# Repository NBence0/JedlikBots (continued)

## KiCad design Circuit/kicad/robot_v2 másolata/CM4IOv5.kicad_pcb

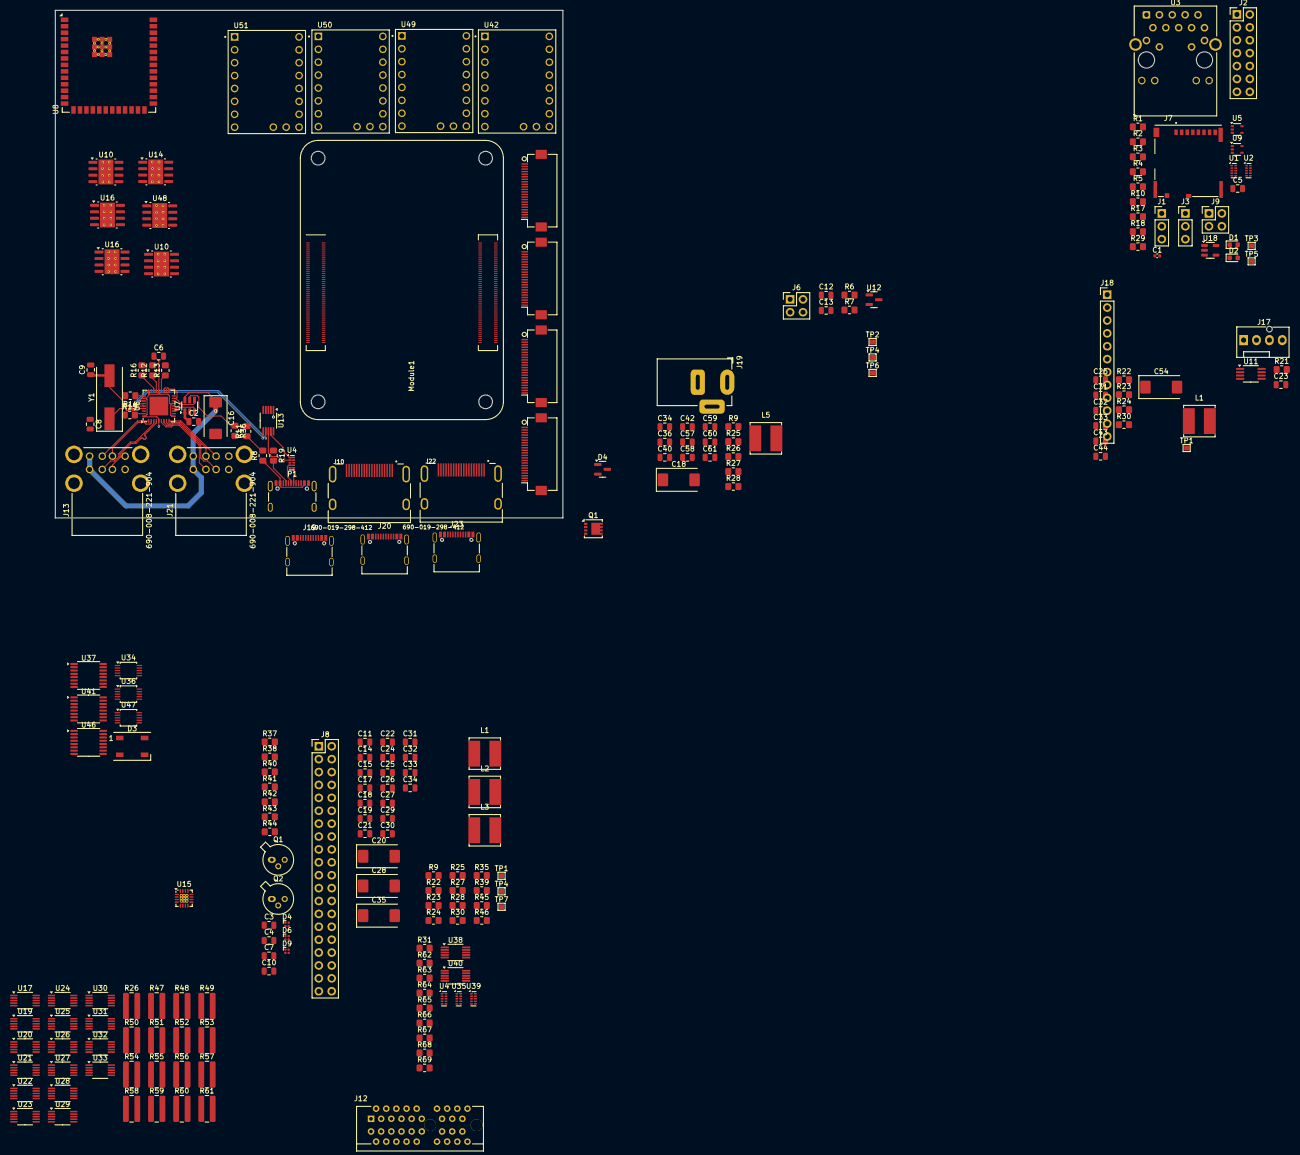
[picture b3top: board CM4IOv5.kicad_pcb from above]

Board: 4 copper layers, 100.0 x 100.0 mm, 226 parts (0 on the bottom side), 295 nets.

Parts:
C1: 100n; C_0402_1005Metric
C2, C5: 10u; C_0805_2012Metric
C3, C7: 100nf; C_0805_2012Metric
C4: 1uf; C_0805_2012Metric
C6: 100u; C_0805_2012Metric
C8, C9: 27pF; C_0805_2012Metric
C10: 100uf; C_0805_2012Metric
C11, C21, C25, C29, C34#2, C42: 10u 35v; C_0805_2012Metric
C12, C13, C14, C15, C22, C23, C24, C30, C31, C31#2, C32, C40, C57, C58: 100n; C_0805_2012Metric
C16, C18#2, C20, C28, C35, C54: 100uF; CP_EIA-7343-31_Kemet-D
C17, C19, C25#2, C27, C32#2, C33#2, C34, C44, C59, C61: nf; C_0805_2012Metric
C18, C26, C33, C43, C60: 1.2nF; C_0805_2012Metric
C36: 100n 100v; C_0805_2012Metric
D1: LED Red; LED_0603_1608Metric
D2: LED Green; LED_0603_1608Metric
D3: WS2812B; LED_WS2812B_PLCC4_5.0x5.0mm_P3.2mm
D4, D6, D9: LED; LED_Lumex_SML-LX0303SIUPGUSB
D4#2: MMBZ5242BLT3G; SOT-23
J1, J3: Conn_01x03; PinHeader_1x03_P2.54mm_Vertical
J2: Conn_02x07_Odd_Even; PinHeader_2x07_P2.54mm_Vertical
J4, J5, J15, J16: Conn_01x22_Female; Hirose_FH12-22S-0.5SH_1x22-1MP_P0.50mm_Horizontal
J6, J9: THD-02-R; PinHeader_2x02_P2.54mm_Vertical
J7: Micro_SD_Card_Det; SDCARD_MOLEX_503398-1892
J8: THD-20-R; PinHeader_2x20_P2.54mm_Vertical
J10, J22: 690-019-298-412; EDAC 690-019-298-412
J12: 10018783-11200TLF; PCIex1-36
J13, J21: 690-008-221-904; MOLEX_USB_67298-4090
J17: Molex 470531000; FanPinHeader_1x04_P2.54mm_Vertical
J18: Conn_01x12_Pin; PinHeader_1x12_P2.54mm_Vertical
J19, J20, J23: USB_C_Receptacle_USB2.0_16P; USB_C_Receptacle_Palconn_UTC16-G
J19#2: Barrel_Jack; BarrelJack_Horizontal
L1, L1#2, L2, L3, L5: SRN6045TA-3R3Y; L_Bourns_SRN6045TA
Module1: ComputeModule4; Raspberry-Pi-4-Compute-Module
P1: USB_C_Plug_USB2.0; USB_C_Receptacle_GCT_USB4105-xx-A_16P_TopMnt_Horizontal
Q1: DMP3013SFV-7; Diodes_PowerDI3333-8
Q1#2, Q2: SS8050-G; TO-18-3_Lens
R1, R10, R37, R38, R44: 1k; R_0805_2012Metric_Pad1.20x1.40mm_HandSolder
R2, R3: 470R; R_0805_2012Metric_Pad1.20x1.40mm_HandSolder
R4, R17, R18: nf; R_0805_2012Metric_Pad1.20x1.40mm_HandSolder
R5: 0R; R_0805_2012Metric_Pad1.20x1.40mm_HandSolder
R6, R7, R8, R11, R28, R28#2, R62, R63, R66, R67: 2.2K 1%; R_0805_2012Metric_Pad1.20x1.40mm_HandSolder
R9, R9#2, R22, R22#2, R35: 10R; R_0805_2012Metric_Pad1.20x1.40mm_HandSolder
R12, R13, R14, R16, R21: 36K 1%; R_0805_2012Metric_Pad1.20x1.40mm_HandSolder
R15, R23, R23#2, R25, R26, R27, R27#2, R29: 12K 1%; R_0805_2012Metric_Pad1.20x1.40mm_HandSolder
R19, R31, R64, R65, R68, R69: 5.1K 1%; R_0805_2012Metric_Pad1.20x1.40mm_HandSolder
R24, R24#2: 47K 1%; R_0805_2012Metric_Pad1.20x1.40mm_HandSolder
R25#2: 20K 1%; R_0805_2012Metric_Pad1.20x1.40mm_HandSolder
R26#2, R47, R48, R49, R50, R51, R52, R53, R54, R55, R56, R57, R58, R59, R60, R61: 0.025Ω; R_1020_2550Metric
R30, R30#2, R36: 15K 1%; R_0805_2012Metric_Pad1.20x1.40mm_HandSolder
R39: 33K 1%; R_0805_2012Metric_Pad1.20x1.40mm_HandSolder
R40, R41, R42, R43: 10k; R_0805_2012Metric_Pad1.20x1.40mm_HandSolder
R45: 13K 1%; R_0805_2012Metric_Pad1.20x1.40mm_HandSolder
R46: 110K 1%; R_0805_2012Metric_Pad1.20x1.40mm_HandSolder
TP1, TP1#2, TP2, TP3, TP4, TP4#2, TP5, TP6, TP7: TestPoint; TestPoint_Pad_1.0x1.0mm
U1, U2, U4, U4#2, U35, U39: TPD4EUSB30; USON-10_2.5x1.0mm_P0.5mm
U3: MagJack-A70-112-331N126; TRJG0926HENL
U5, U9: 74LVC1G07SE-7; SOT-353_SC-70-5
U6: USB2514B-I/M2; QFN-36-1EP_6x6mm_P0.5mm_EP3.7x3.7mm
U7: AP22653W6; SOT-23-6
U8: ESP32-S3-WROOM-2
U10, U10#2, U14, U16, U16#2, U48: AP64501SP-13; SOIC-8-1EP_3.9x4.9mm_P1.27mm_EP2.95x4.9mm_Mask2.71x3.4mm_Th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
U11: EMC2301-1-ACZL-TR; MSOP-8_3x3mm_P0.65mm
U12: RT9742SNGV; SOT-23
U13, U38, U40: FSUSB42MUX; MSOP-10_3x3mm_P0.5mm
U15: CH343P; QFN-16-1EP_3x3mm_P0.5mm_EP1.7x1.7mm_ThermalVias
U17, U19, U20, U21, U22, U23, U24, U25, U26, U27, U28, U29, U30, U31, U32, U33: INA226; VSSOP-10_3x3mm_P0.5mm
U18: RT9742GGJ5; SOT-23-5
U34, U36, U47: ADS1115IDGS; TSSOP-10_3x3mm_P0.5mm
U37, U41, U46: ADC1283; TSSOP-16_4.4x5mm_P0.65mm
U42, U49, U50, U51: TMC2240_SILENTSTEPSTICK; MODULE_TMC2209_SILENTSTEPSTICK
Y1: 24MHz; Crystal_SMD_HC49-SD

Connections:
5V1: U17.1 (A1), U17.2 (A0), U17.6 (VS), U19.1 (A1), U19.6 (VS), U20.6 (VS), U21.6 (VS), U22.2 (A0), U22.6 (VS), U23.6 (VS), U24.1 (A1), U24.6 (VS), U25.6 (VS), U26.2 (A0), U26.6 (VS), U27.6 (VS), U28.6 (VS), U29.6 (VS), U30.6 (VS), U31.6 (VS), U32.1 (A1), U32.6 (VS), U33.2 (A0), U33.6 (VS)
/+3.3v: D1.2 (A), D2.2 (A), J4.22, J5.22, J8.1, J8.17, J15.22, J16.22, J18.4, Module1.84 (+3.3v_(Output)), Module1.86 (+3.3v_(Output)), R5.1, R17.1, R29.1, U3.15 (LEDG_A), U3.17 (LEDY_A), U5.5 (VCC), U18.5 (IN)
/+5v: C12.1, C18#2.1, C61.1, J8.2, J8.4, J18.3, L5.2, Module1.77 (+5v_(Input)), Module1.79 (+5v_(Input)), Module1.81 (+5v_(Input)), Module1.83 (+5v_(Input)), Module1.85 (+5v_(Input)), Module1.87 (+5v_(Input)), R27.1, TP4.1, U9.5 (VCC), U12.1 (IN)
/+12v: C34#2.1, C40.1, C42.1, D4#2.3 (K), J18.2, Q1.1 (S), Q1.2 (S), Q1.3 (S), TP2.1, U16.2 (VIN), U16.3 (EN)
/CM4_GPIO ( Ethernet, GPIO, SDCARD)/+1.8v: Module1.88 (+1.8v_(Output)), Module1.90 (+1.8v_(Output)), R4.1
/CM4_GPIO ( Ethernet, GPIO, SDCARD)/AIN0: J2.5, Module1.96 (AnalogIP0)
/CM4_GPIO ( Ethernet, GPIO, SDCARD)/AIN1: J2.6, Module1.94 (AnalogIP1)
/CM4_GPIO ( Ethernet, GPIO, SDCARD)/BT_nDis: J3.3, Module1.91 (BT_nDisable)
/CM4_GPIO ( Ethernet, GPIO, SDCARD)/EEPROM_nWP: J2.4, Module1.20 (EEPROM_nWP)
/CM4_GPIO ( Ethernet, GPIO, SDCARD)/ETH_LEDG: Module1.17 (Ethernet_nLED2(3.3v)), R2.2
/CM4_GPIO ( Ethernet, GPIO, SDCARD)/ETH_LEDY: Module1.15 (Ethernet_nLED3(3.3v)), R3.2
/CM4_GPIO ( Ethernet, GPIO, SDCARD)/GLOBAL_EN: J1.1, J2.14, Module1.99 (Global_EN)
/CM4_GPIO ( Ethernet, GPIO, SDCARD)/GPIO2: J8.3, Module1.58 (GPIO2)
/CM4_GPIO ( Ethernet, GPIO, SDCARD)/GPIO3: J8.5, Module1.56 (GPIO3)
/CM4_GPIO ( Ethernet, GPIO, SDCARD)/GPIO4: J8.7, Module1.54 (GPIO4)
/CM4_GPIO ( Ethernet, GPIO, SDCARD)/GPIO5: J8.29, Module1.34 (GPIO5)
/CM4_GPIO ( Ethernet, GPIO, SDCARD)/GPIO6: J8.31, Module1.30 (GPIO6)
/CM4_GPIO ( Ethernet, GPIO, SDCARD)/GPIO7: J8.26, Module1.37 (GPIO7)
/CM4_GPIO ( Ethernet, GPIO, SDCARD)/GPIO8: J8.24, Module1.39 (GPIO8)
/CM4_GPIO ( Ethernet, GPIO, SDCARD)/GPIO9: J8.21, Module1.40 (GPIO9)
/CM4_GPIO ( Ethernet, GPIO, SDCARD)/GPIO10: J8.19, Module1.44 (GPIO10)
/CM4_GPIO ( Ethernet, GPIO, SDCARD)/GPIO11: J8.23, Module1.38 (GPIO11)
/CM4_GPIO ( Ethernet, GPIO, SDCARD)/GPIO12: J8.32, Module1.31 (GPIO12)
/CM4_GPIO ( Ethernet, GPIO, SDCARD)/GPIO13: J8.33, Module1.28 (GPIO13)
/CM4_GPIO ( Ethernet, GPIO, SDCARD)/GPIO14: J8.8, Module1.55 (GPIO14)
/CM4_GPIO ( Ethernet, GPIO, SDCARD)/GPIO15: J8.10, Module1.51 (GPIO15)
/CM4_GPIO ( Ethernet, GPIO, SDCARD)/GPIO16: J8.36, Module1.29 (GPIO16)
/CM4_GPIO ( Ethernet, GPIO, SDCARD)/GPIO17: J8.11, Module1.50 (GPIO17)
/CM4_GPIO ( Ethernet, GPIO, SDCARD)/GPIO18: J8.12, Module1.49 (GPIO18)
/CM4_GPIO ( Ethernet, GPIO, SDCARD)/GPIO19: J8.35, Module1.26 (GPIO19)
/CM4_GPIO ( Ethernet, GPIO, SDCARD)/GPIO20: J8.38, Module1.27 (GPIO20)
/CM4_GPIO ( Ethernet, GPIO, SDCARD)/GPIO21: J8.40, Module1.25 (GPIO21)
/CM4_GPIO ( Ethernet, GPIO, SDCARD)/GPIO22: J8.15, Module1.46 (GPIO22)
/CM4_GPIO ( Ethernet, GPIO, SDCARD)/GPIO23: J8.16, Module1.47 (GPIO23)
/CM4_GPIO ( Ethernet, GPIO, SDCARD)/GPIO24: J8.18, Module1.45 (GPIO24)
/CM4_GPIO ( Ethernet, GPIO, SDCARD)/GPIO25: J8.22, Module1.41 (GPIO25)
/CM4_GPIO ( Ethernet, GPIO, SDCARD)/GPIO26: J8.37, Module1.24 (GPIO26)
/CM4_GPIO ( Ethernet, GPIO, SDCARD)/GPIO27: J8.13, Module1.48 (GPIO27)
/CM4_GPIO ( Ethernet, GPIO, SDCARD)/GPIO_VREF: Module1.78 (GPIO_VREF(1.8v/3.3v_Input)), R4.2, R5.2, R6.1, R7.1
/CM4_GPIO ( Ethernet, GPIO, SDCARD)/ID_SC: J6.1, J8.28, Module1.35 (ID_SC)
/CM4_GPIO ( Ethernet, GPIO, SDCARD)/ID_SD: J6.3, J8.27, Module1.36 (ID_SD)
/CM4_GPIO ( Ethernet, GPIO, SDCARD)/RUN_PG: J1.3, Module1.92 (RUN_PG), U9.2
/CM4_GPIO ( Ethernet, GPIO, SDCARD)/Reserved: Module1.76 (Reserved), R18.1
/CM4_GPIO ( Ethernet, GPIO, SDCARD)/SD_CLK: J7.5 (CLK), Module1.57 (SD_CLK)
/CM4_GPIO ( Ethernet, GPIO, SDCARD)/SD_CMD: J7.3 (CMD), Module1.62 (SD_CMD)
/CM4_GPIO ( Ethernet, GPIO, SDCARD)/SD_DAT0: J7.7 (DAT0), Module1.63 (SD_DAT0)
/CM4_GPIO ( Ethernet, GPIO, SDCARD)/SD_DAT1: J7.8 (DAT1), Module1.67 (SD_DAT1)
/CM4_GPIO ( Ethernet, GPIO, SDCARD)/SD_DAT2: J7.1 (DAT2), Module1.69 (SD_DAT2)
/CM4_GPIO ( Ethernet, GPIO, SDCARD)/SD_DAT3: J7.2 (DAT3/CD), Module1.61 (SD_DAT3)
/CM4_GPIO ( Ethernet, GPIO, SDCARD)/SD_PWR: C5.1, J7.4 (VDD), U18.1 (OUT)
/CM4_GPIO ( Ethernet, GPIO, SDCARD)/SD_PWR_ON: Module1.75 (SD_PWR_ON), R29.2, U18.4 (EN)
/CM4_GPIO ( Ethernet, GPIO, SDCARD)/SYNC_IN: J2.8, Module1.16 (Ethernet_SYNC_IN(1.8v))
/CM4_GPIO ( Ethernet, GPIO, SDCARD)/SYNC_OUT: J2.9, Module1.18 (Ethernet_SYNC_OUT(1.8v))
/CM4_GPIO ( Ethernet, GPIO, SDCARD)/TR0_TAP: J9.3, U3.11 (VC1)
/CM4_GPIO ( Ethernet, GPIO, SDCARD)/TR1_TAP: J9.1, U3.12 (VC2)
/CM4_GPIO ( Ethernet, GPIO, SDCARD)/TR2_TAP: J9.2, U3.13 (VC3)
/CM4_GPIO ( Ethernet, GPIO, SDCARD)/TR3_TAP: J9.4, U3.14 (VC4)
/CM4_GPIO ( Ethernet, GPIO, SDCARD)/TRD0_N: Module1.10 (Ethernet_Pair0_N), U2.4 (D2+), U2.7, U3.2 (TRD0-)
/CM4_GPIO ( Ethernet, GPIO, SDCARD)/TRD0_P: Module1.12 (Ethernet_Pair0_P), U2.5 (D2-), U2.6, U3.1 (TRD0+)
/CM4_GPIO ( Ethernet, GPIO, SDCARD)/TRD1_N: Module1.6 (Ethernet_Pair1_N), U2.2 (D1-), U2.9, U3.6 (TRD1-)
/CM4_GPIO ( Ethernet, GPIO, SDCARD)/TRD1_P: Module1.4 (Ethernet_Pair1_P), U2.1 (D1+), U2.10, U3.3 (TRD1+)
/CM4_GPIO ( Ethernet, GPIO, SDCARD)/TRD2_N: Module1.9 (Ethernet_Pair2_N), U1.4 (D2+), U1.7, U3.8 (TRD2-)
/CM4_GPIO ( Ethernet, GPIO, SDCARD)/TRD2_P: Module1.11 (Ethernet_Pair2_P), U1.5 (D2-), U1.6, U3.7 (TRD2+)
/CM4_GPIO ( Ethernet, GPIO, SDCARD)/TRD3_N: Module1.5 (Ethernet_Pair3_N), U1.2 (D1-), U1.9, U3.10 (TRD3-)
/CM4_GPIO ( Ethernet, GPIO, SDCARD)/TRD3_P: Module1.3 (Ethernet_Pair3_P), U1.1 (D1+), U1.10, U3.9 (TRD3+)
/CM4_GPIO ( Ethernet, GPIO, SDCARD)/TV_OUT: J2.11, Module1.111 (VDAC_COMP)
/CM4_GPIO ( Ethernet, GPIO, SDCARD)/WL_nDis: J3.1, Module1.89 (WiFi_nDisable)
/CM4_GPIO ( Ethernet, GPIO, SDCARD)/nPWR_LED: Module1.95 (nPI_LED_PWR), U5.2
/CM4_GPIO ( Ethernet, GPIO, SDCARD)/nRPIBOOT: J2.2, Module1.93 (nRPIBOOT)
/CM4_HighSpeed/CAM0_C_N: J4.8, Module1.140 (CAM0_C_N)
/CM4_HighSpeed/CAM0_C_P: J4.9, Module1.142 (CAM0_C_P)
/CM4_HighSpeed/CAM0_D0_N: J4.2, Module1.128 (CAM0_D0_N)
/CM4_HighSpeed/CAM0_D0_P: J4.3, Module1.130 (CAM0_D0_P)
/CM4_HighSpeed/CAM0_D1_N: J4.5, Module1.134 (CAM0_D1_N)
/CM4_HighSpeed/CAM0_D1_P: J4.6, Module1.136 (CAM0_D1_P)
/CM4_HighSpeed/CAM1_C_N: J5.8, Module1.127 (CAM1_C_N)
/CM4_HighSpeed/CAM1_C_P: J5.9, Module1.129 (CAM1_C_P)
/CM4_HighSpeed/CAM1_D0_N: J5.2, Module1.115 (CAM1_D0_N)
/CM4_HighSpeed/CAM1_D0_P: J5.3, Module1.117 (CAM1_D0_P)
/CM4_HighSpeed/CAM1_D1_N: J5.5, Module1.121 (CAM1_D1_N)
/CM4_HighSpeed/CAM1_D1_P: J5.6, Module1.123 (CAM1_D1_P)
/CM4_HighSpeed/CAM1_D2_N: J5.11, Module1.133 (CAM1_D2_N)
/CM4_HighSpeed/CAM1_D2_P: J5.12, Module1.135 (CAM1_D2_P)
/CM4_HighSpeed/CAM1_D3_N: J5.14, Module1.139 (CAM1_D3_N)
/CM4_HighSpeed/CAM1_D3_P: J5.15, Module1.141 (CAM1_D3_P)
/CM4_HighSpeed/CAM_GPIO: J4.17, J5.17, Module1.97 (Camera_GPIO)
/CM4_HighSpeed/DSI0_C_N: J15.8, Module1.169 (DSI0_C_N)
/CM4_HighSpeed/DSI0_C_P: J15.9, Module1.171 (DSI0_C_P)
/CM4_HighSpeed/DSI0_D0_N: J15.2, Module1.157 (DSI0_D0_N)
/CM4_HighSpeed/DSI0_D0_P: J15.3, Module1.159 (DSI0_D0_P)
/CM4_HighSpeed/DSI0_D1_N: J15.5, Module1.163 (DSI0_D1_N)
/CM4_HighSpeed/DSI0_D1_P: J15.6, Module1.165 (DSI0_D1_P)
/CM4_HighSpeed/DSI1_C_N: J16.8, Module1.187 (DSI1_C_N)
/CM4_HighSpeed/DSI1_C_P: J16.9, Module1.189 (DSI1_C_P)
/CM4_HighSpeed/DSI1_D0_N: J16.2, Module1.175 (DSI1_D0_N)
/CM4_HighSpeed/DSI1_D0_P: J16.3, Module1.177 (DSI1_D0_P)
/CM4_HighSpeed/DSI1_D1_N: J16.5, Module1.181 (DSI1_D1_N)
/CM4_HighSpeed/DSI1_D1_P: J16.6, Module1.183 (DSI1_D1_P)
/CM4_HighSpeed/DSI1_D2_N: J16.11, Module1.193 (DSI1_D2_N)
/CM4_HighSpeed/DSI1_D2_P: J16.12, Module1.195 (DSI1_D2_P)
/CM4_HighSpeed/DSI1_D3_N: J16.14, Module1.194 (DSI1_D3_N)
/CM4_HighSpeed/DSI1_D3_P: J16.15, Module1.196 (DSI1_D3_P)
/CM4_HighSpeed/HDMI0_CEC: J22.13 (CEC), Module1.151 (HDMI0_CEC)
/CM4_HighSpeed/HDMI0_CK_N: J22.12 (CK-), Module1.190 (HDMI0_CLK_N)
/CM4_HighSpeed/HDMI0_CK_P: J22.10 (CK+), Module1.188 (HDMI0_CLK_P)
/CM4_HighSpeed/HDMI0_D0_N: J22.9 (D0-), Module1.184 (HDMI0_TX0_N)
/CM4_HighSpeed/HDMI0_D0_P: J22.7 (D0+), Module1.182 (HDMI0_TX0_P)
/CM4_HighSpeed/HDMI0_D1_N: J22.6 (D1-), Module1.178 (HDMI0_TX1_N)
/CM4_HighSpeed/HDMI0_D1_P: J22.4 (D1+), Module1.176 (HDMI0_TX1_P)
/CM4_HighSpeed/HDMI0_D2_N: J22.3 (D2-), Module1.172 (HDMI0_TX2_N)
/CM4_HighSpeed/HDMI0_D2_P: J22.1 (D2+), Module1.170 (HDMI0_TX2_P)
/CM4_HighSpeed/HDMI0_HOTPLUG: J22.19 (HPD/HEAC-), Module1.153 (HDMI0_HOTPLUG)
/CM4_HighSpeed/HDMI0_SCL: J22.15 (SCL), Module1.200 (HDMI0_SCL)
/CM4_HighSpeed/HDMI0_SDA: J22.16 (SDA), Module1.199 (HDMI0_SDA)
/CM4_HighSpeed/HDMI1_CEC: J10.13 (CEC), Module1.149 (HDMI1_CEC)
/CM4_HighSpeed/HDMI1_CK_N: J10.12 (CK-), Module1.166 (HDMI1_CLK_N)
/CM4_HighSpeed/HDMI1_CK_P: J10.10 (CK+), Module1.164 (HDMI1_CLK_P)
/CM4_HighSpeed/HDMI1_D0_N: J10.9 (D0-), Module1.160 (HDMI1_TX0_N)
/CM4_HighSpeed/HDMI1_D0_P: J10.7 (D0+), Module1.158 (HDMI1_TX0_P)
/CM4_HighSpeed/HDMI1_D1_N: J10.6 (D1-), Module1.154 (HDMI1_TX1_N)
/CM4_HighSpeed/HDMI1_D1_P: J10.4 (D1+), Module1.152 (HDMI1_TX1_P)
/CM4_HighSpeed/HDMI1_D2_N: J10.3 (D2-), Module1.148 (HDMI1_TX2_N)
/CM4_HighSpeed/HDMI1_D2_P: J10.1 (D2+), Module1.146 (HDMI1_TX2_P)
/CM4_HighSpeed/HDMI1_HOTPLUG: J10.19 (HPD/HEAC-), Module1.143 (HDMI1_HOTPLUG)
/CM4_HighSpeed/HDMI1_SCL: J10.15 (SCL), Module1.147 (HDMI1_SCL)
/CM4_HighSpeed/HDMI1_SDA: J10.16 (SDA), Module1.145 (HDMI1_SDA)
/CM4_HighSpeed/HDMI_5v: C13.1, J10.18 (+5V), J22.18 (+5V), U12.2 (OUT)
/CM4_HighSpeed/PCIE_CLK_N: J18.10, Module1.112 (PCIe_CLK_N)
/CM4_HighSpeed/PCIE_CLK_P: J18.9, Module1.110 (PCIe_CLK_P)
/CM4_HighSpeed/PCIE_CLK_nREQ: J18.12, Module1.102 (PCIe_CLK_nREQ)
/CM4_HighSpeed/PCIE_RX_N: J18.8, Module1.118 (PCIe_RX_N)
/CM4_HighSpeed/PCIE_RX_P: J18.7, Module1.116 (PCIe_RX_P)
/CM4_HighSpeed/PCIE_TX_N: J18.6, Module1.124 (PCIe_TX_N)
/CM4_HighSpeed/PCIE_TX_P: J18.5, Module1.122 (PCIe_TX_P)
/CM4_HighSpeed/PCIE_nRST: J18.11, Module1.109 (PCIe_nRST)
/CM4_HighSpeed/SCL0: J5.20, J16.20, Module1.80 (SCL0), U11.2 (SCL)
/CM4_HighSpeed/SCL1: J4.20, J6.2, J15.20, R7.2
/CM4_HighSpeed/SDA0: J5.21, J16.21, Module1.82 (SDA0), U11.1 (SDA)
/CM4_HighSpeed/SDA1: J4.21, J6.4, J15.21, R6.2
/CM4_HighSpeed/USB2_N: Module1.103 (USB2_N), U13.4 (D_N)
/CM4_HighSpeed/USB2_P: Module1.105 (USB2_P), U13.3 (D_P)
/CM4_HighSpeed/USBOTG_ID: Module1.101 (USB_OTG_ID), R8.2, R11.1, U13.2 (SEL)
/FAN/+3.3v: C23.1, R21.2, U11.3 (VDD)
/INA226/+1000000: R48.1, U20.8 (Vbus), U20.10 (Vin+)
/INA226/+1000001: R61.1, U33.8 (Vbus), U33.10 (Vin+)
/INA226/+1000010: R58.1, U30.8 (Vbus), U30.10 (Vin+)
/INA226/+1000011: R57.1, U29.8 (Vbus), U29.10 (Vin+)
/INA226/+1000100: R52.1, U24.8 (Vbus), U24.10 (Vin+)
/INA226/+1000101: R26#2.1, U17.8 (Vbus), U17.10 (Vin+)
/INA226/+1000110: R60.1, U32.8 (Vbus), U32.10 (Vin+)
/INA226/+1000111: R47.1, U19.8 (Vbus), U19.10 (Vin+)
/INA226/+1001000: R56.1, U28.8 (Vbus), U28.10 (Vin+)
/INA226/+1001001: R50.1, U22.8 (Vbus), U22.10 (Vin+)
/INA226/+1001010: R49.1, U21.8 (Vbus), U21.10 (Vin+)
/INA226/+1001011: R51.1, U23.8 (Vbus), U23.10 (Vin+)
/INA226/+1001100: R59.1, U31.8 (Vbus), U31.10 (Vin+)
/INA226/+1001101: R54.1, U26.8 (Vbus), U26.10 (Vin+)
/INA226/+1001110: R53.1, U25.8 (Vbus), U25.10 (Vin+)
/INA226/+1001111: R55.1, U27.8 (Vbus), U27.10 (Vin+)
/INA226/-1000000: R48.2, U20.9 (Vin-)
/INA226/-1000001: R61.2, U33.9 (Vin-)
/INA226/-1000010: R58.2, U30.9 (Vin-)
/INA226/-1000011: R57.2, U29.9 (Vin-)
/INA226/-1000100: R52.2, U24.9 (Vin-)
/INA226/-1000101: R26#2.2, U17.9 (Vin-)
/INA226/-1000110: R60.2, U32.9 (Vin-)
/INA226/-1000111: R47.2, U19.9 (Vin-)
/INA226/-1001000: R56.2, U28.9 (Vin-)
/INA226/-1001001: R50.2, U22.9 (Vin-)
/INA226/-1001010: R49.2, U21.9 (Vin-)
/INA226/-1001011: R51.2, U23.9 (Vin-)
/INA226/-1001100: R59.2, U31.9 (Vin-)
/INA226/-1001101: R54.2, U26.9 (Vin-)
/INA226/-1001110: R53.2, U25.9 (Vin-)
/INA226/-1001111: R55.2, U27.9 (Vin-)
/INA226/alert out: U17.3 (~Alert), U19.3 (~Alert), U20.3 (~Alert), U21.3 (~Alert), U22.3 (~Alert), U23.3 (~Alert), U24.3 (~Alert), U25.3 (~Alert), U26.3 (~Alert), U27.3 (~Alert), U28.3 (~Alert), U29.3 (~Alert), U30.3 (~Alert), U31.3 (~Alert), U32.3 (~Alert), U33.3 (~Alert)
/PCIe-connector/+3.3v: C44.1, C54.1, J12.A5 (TCK), J12.A6 (TDI), J12.A8 (TMS), J12.A9 (+3.3V), J12.A10 (+3.3V), J12.B8 (+3.3v), J12.B9 (nTRST), J12.B10 (+3.3vAUX), L1.2, R24.1, TP1#2.1
/PCIe-connector/+12v: C25.1, J12.A2 (+12V), J12.A3 (+12V), J12.B1 (+12v), J12.B2 (+12v), J12.B3 (+12v), U10#2.2 (VIN), U10#2.3 (EN)
/PSUs/3V3: C27.1, C28.1, L1#2.2, R24#2.1, TP1.1
/PSUs/5v: C19.1, C20.1, L2.2, R27#2.1, TP4#2.1
/PSUs/7V5: C34.1, C35.1, L3.2, R45.1, TP7.1
/PSUs/input voltage: C11.1, C21.1, C29.1, U10.2 (VIN), U14.2 (VIN), U16#2.2 (VIN)
/USB2-HUB/+3.3v: C6.1, U6.5 (VDDA33), U6.10 (VDDA33), U6.15 (VDD33), U6.23 (VDD33), U6.27 (VBUS_DET), U6.29 (VDDA33), U6.36 (VDDA33), U13.1 (VCC), U38.1 (VCC), U40.1 (VCC)
/USB2-HUB/+5v: C2.1, U7.1 (IN)
/USB2-HUB/CH343P_usbD+: U15.7 (UD+), U40.3 (D_P)
/USB2-HUB/CH343P_usbD-: U15.8 (UD-), U40.4 (D_N)
/USB2-HUB/ESP_usbD+: U8.14 (USB_D+/IO20), U38.3 (D_P)
/USB2-HUB/ESP_usbD-: U8.13 (USB_D-/IO19), U38.4 (D_N)
/USB2-HUB/HD1_N: J13.2 (D-`), U6.1 (USBDM_DN1/PRT_DIS_M1), U35.5 (D2-), U35.6
/USB2-HUB/HD1_P: J13.3 (D+`), U6.2 (USBDP_DN1/PRT_DIS_P1), U35.4 (D2+), U35.7
/USB2-HUB/HD2_N: J13.6 (D-), U6.3 (USBDM_DN2/PRT_DIS_M2), U35.2 (D1-), U35.9
/USB2-HUB/HD2_P: J13.7 (D+), U6.4 (USBDP_DN2/PRT_DIS_P2), U35.1 (D1+), U35.10
/USB2-HUB/HD3_N: J21.6 (D-), U6.6 (USBDM_DN3/PRT_DIS_M3), U40.6 (HSD0_M)
/USB2-HUB/HD3_P: J21.7 (D+), U6.7 (USBDP_DN3/PRT_DIS_P3), U40.7 (HSD0_P)
/USB2-HUB/HD4_N: J21.2 (D-`), U6.8 (USBDM_DN4/PRT_DIS_M4), U38.6 (HSD0_M)
/USB2-HUB/HD4_P: J21.3 (D+`), U6.9 (USBDP_DN4/PRT_DIS_P4), U38.7 (HSD0_P)
/USB2-HUB/PWR1: U6.12 (PRTPWR1/BC_EN1), U7.3 (EN)
/USB2-HUB/USBD_N: J23.A6 (D+), J23.B6 (D+), U4.2 (D1-), U4.9, U4#2.2 (D1-), U4#2.9, U13.8 (HSD1_M)
/USB2-HUB/USBD_P: J23.A7 (D-), J23.B7 (D-), U4.1 (D1+), U4.10, U4#2.1 (D1+), U4#2.10, U13.9 (HSD1_P)
/USB2-HUB/USBH_N: U6.30 (USBDM_UP), U13.6 (HSD0_M)
/USB2-HUB/USBH_P: U6.31 (USBDP_UP), U13.7 (HSD0_P)
/USB2-HUB/VBUS: C16.1, J13.1 (VBUS`), J13.5 (VBUS), J21.1 (VBUS`), J21.5 (VBUS), U7.6 (OUT)
/USB2-HUB/nOCS1: U6.13 (OCS_N1), U6.17 (OCS_N2), U6.19 (OCS_N3), U6.21 (OCS_N4), U7.4 (nFault)
/YD-ESP32-S3/3v3-input: C7.1, C10.1, R37.2, R38.2, R42.2, R43.1, R44.2, U8.2 (3V3), U15.1 (VIO)
/YD-ESP32-S3/5 v In: U15.3 (VDD5), U15.9 (VBUS)
/YD-ESP32-S3/esp32_chip_pu: C4.1, Q2.3 (C), R42.1, U8.3 (EN)
/YD-ESP32-S3/esp32_gpio0: Q1#2.3 (C), U8.27 (IO0)
/YD-ESP32-S3/esp_rxd0: D9.1 (K), U8.36 (RXD0/IO44)
/YD-ESP32-S3/esp_txd0: D6.1 (K), U8.37 (TXD0/IO43), U15.4 (TXD), U15.5 (RXD)
/nEXTRST: Module1.100 (nEXTRST), U6.26 (RESET_N)
GND: C1.2, C2.2, C3.2, C4.2, C5.2, C6.2, C7.2, C8.2, C9.2, C10.2, C11.2, C12.2, C13.2, C15.2, C16.2, C17.2, C18.2, C18#2.2, C20.2, C21.2, C23.2, C24.2, C25.2, C25#2.2, C26.2, C28.2, C29.2, C31#2.2, C32.2, C32#2.2, C33.2, C33#2.2, C34#2.2, C35.2, C36.2, C42.2, C43.2, C54.2, C58.2, C59.2, C60.2, J1.2, J2.1, J2.3, J2.7, J2.10, J2.12, J3.2, J4.1, J4.4, J4.7, J4.10, J4.13, J4.16, J4.19, J5.1, J5.4, J5.7, J5.10, J5.13, J5.16, J5.19, J7.6 (VSS), J7.11 (SHIELD), J8.6, J8.9, J8.14, J8.20, J8.25, J8.30, J8.34, J8.39, J10.2 (D2S), J10.5 (D1S), J10.8 (D0S), J10.11 (CKS), J10.17 (GND), J10.SH1 (SH), J10.SH2 (SH), J10.SH3 (SH), J10.SH4 (SH), J12.A4 (GND), J12.A12 (GND), J12.A15 (GND), J12.A18 (GND), J12.B4 (GND), J12.B7 (GND), J12.B13 (GND), J12.B16 (GND), J12.B18 (GND), J13.4 (GND`), J13.8 (GND), J13.MT1, J13.MT2, J13.MT3, J13.MT4, J15.1, J15.4, J15.7, J15.10, J15.13, J15.16, J15.19, J16.1, J16.4, J16.7, J16.10, J16.13, J16.16, J16.19, J17.1, J18.1, J19.A1 (GND), J19.A12 (GND), J19.B1 (GND), J19.B12 (GND), J19.S1 (SHIELD), J19#2.2, J19#2.3, J20.A1 (GND), J20.A12 (GND), J20.B1 (GND), J20.B12 (GND), J20.S1 (SHIELD), J21.4 (GND`), J21.8 (GND), J21.MT1, J21.MT2, J21.MT3, J21.MT4, J22.2 (D2S), J22.5 (D1S), J22.8 (D0S), J22.11 (CKS), J22.17 (GND), J22.SH1 (SH), J22.SH2 (SH), J22.SH3 (SH), J22.SH4 (SH), J23.A1 (GND), J23.A12 (GND), J23.B1 (GND), J23.B12 (GND), J23.S1 (SHIELD), Module1.1 (GND), Module1.2 (GND), Module1.7 (GND), Module1.8 (GND), Module1.13 (GND), Module1.14 (GND), Module1.22 (GND), Module1.23 (GND), Module1.32 (GND), Module1.33 (GND), Module1.42 (GND), Module1.43 (GND), Module1.52 (GND), Module1.53 (GND), Module1.59 (GND), Module1.60 (GND), Module1.65 (GND), Module1.66 (GND), Module1.71 (GND), Module1.74 (GND), Module1.98 (GND), Module1.107 (GND), Module1.108 (GND), Module1.113 (GND), Module1.114 (GND), Module1.119 (GND), Module1.120 (GND), Module1.125 (GND), Module1.126 (GND), Module1.131 (GND), Module1.132 (GND), Module1.137 (GND), Module1.138 (GND), Module1.144 (GND), Module1.150 (GND), Module1.155 (GND), Module1.156 (GND), Module1.161 (GND), Module1.162 (GND), Module1.167 (GND), Module1.168 (GND), Module1.173 (GND), Module1.174 (GND), Module1.179 (GND), Module1.180 (GND), Module1.185 (GND), Module1.186 (GND), Module1.191 (GND), Module1.192 (GND), Module1.197 (GND), Module1.198 (GND), P1.A1 (GND), P1.A12 (GND), P1.B1 (GND), P1.B12 (GND), P1.S1 (SHIELD), R11.2, R12.2, R13.2, R14.2, R15.1, R16.2, R19.1, R26.2, R28.2, R28#2.2, R30.2, R30#2.2, R31.1, R36.2, R46.2, R62.2, R64.1, R65.1, R66.2, R68.1, R69.1, TP6.1, U1.3 (GND), U1.8 (GND), U2.3 (GND), U2.8 (GND), U3.19 (SHIELD), U3.20 (SHIELD), U4.3 (GND), U4.8 (GND), U4#2.3 (GND), U4#2.8 (GND), U5.3 (GND), U6.37 (VSS), U7.2 (GND), U8.1 (GND), U8.40 (GND), U8.41 (GND), U9.3 (GND), U10.7 (GND), U10.9 (EP), U10#2.7 (GND), U10#2.9 (EP), U11.4 (GND), U12.3 (GND), U13.5 (GND), U13.10 (nOE), U14.7 (GND), U14.9 (EP), U15.2 (GND), U15.17 (GND), U16.7 (GND), U16.9 (EP), U16#2.7 (GND), U16#2.9 (EP), U17.7 (GND), U18.2 (GND), U19.7 (GND), U20.1 (A1), U20.2 (A0), U20.7 (GND), U21.7 (GND), U22.7 (GND), U23.7 (GND), U24.2 (A0), U24.7 (GND), U25.7 (GND), U26.7 (GND), U27.7 (GND), U28.2 (A0), U28.7 (GND), U29.1 (A1), U29.7 (GND), U30.1 (A1), U30.7 (GND), U31.2 (A0), U31.7 (GND), U32.7 (GND), U33.1 (A1), U33.7 (GND), U38.5 (GND), U38.10 (nOE), U40.5 (GND), U40.10 (nOE)
INA226_SCL: U17.4 (SDA), U19.2 (A0), U19.4 (SDA), U20.4 (SDA), U21.4 (SDA), U22.4 (SDA), U23.2 (A0), U23.4 (SDA), U24.4 (SDA), U25.1 (A1), U25.4 (SDA), U26.1 (A1), U26.4 (SDA), U27.1 (A1), U27.2 (A0), U27.4 (SDA), U28.4 (SDA), U29.2 (A0), U29.4 (SDA), U30.4 (SDA), U31.1 (A1), U31.4 (SDA), U32.4 (SDA), U33.4 (SDA)
INA226_SDA: U17.5 (SCL), U19.5 (SCL), U20.5 (SCL), U21.1 (A1), U21.2 (A0), U21.5 (SCL), U22.1 (A1), U22.5 (SCL), U23.1 (A1), U23.5 (SCL), U24.5 (SCL), U25.2 (A0), U25.5 (SCL), U26.5 (SCL), U27.5 (SCL), U28.1 (A1), U28.5 (SCL), U29.5 (SCL), U30.2 (A0), U30.5 (SCL), U31.5 (SCL), U32.2 (A0), U32.5 (SCL), U33.5 (SCL)
unnamed: C1.1, U3.4 (CT), U3.5 (CT)
unnamed: C14.1, R9#2.2
unnamed: C18.1, R25.2
unnamed: C22.1, R22.2
unnamed: C26.1, R23.2
unnamed: C30.1, R35.2
unnamed: C31.1, R22#2.2
unnamed: C33.1, R39.2
unnamed: C43.1, R23#2.2
unnamed: C57.1, R9.2
unnamed: C60.1, R25#2.2
unnamed: D1.1 (K), R10.1, TP5.1
unnamed: D2.1 (K), R1.1, TP3.1
unnamed: D4.2 (A), R44.1
unnamed: C40.2, D4#2.1 (A), Q1.4 (G), R26.1
unnamed: D6.2 (A), R37.1
unnamed: D9.2 (A), R38.1
unnamed: J2.13, U9.4
unnamed: J7.10 (DET_A), R17.2
unnamed: J7.9 (DET_B), R18.2
unnamed: J17.3, R21.1, U11.6 (TACH)
unnamed: J17.4, U11.5 (PWM)
unnamed: J19.A5 (CC1), R64.2
unnamed: J19.B5 (CC2), R65.2
unnamed: J19.A4 (VBUS), J19.A9 (VBUS), J19.B4 (VBUS), J19.B9 (VBUS), R63.1
unnamed: J20.A5 (CC1), R68.2
unnamed: J20.B5 (CC2), R69.2
unnamed: J20.A4 (VBUS), J20.A9 (VBUS), J20.B4 (VBUS), J20.B9 (VBUS), R67.1
unnamed: J23.A5 (CC1), R19.2
unnamed: J23.B5 (CC2), R31.2
unnamed: J23.A4 (VBUS), J23.A9 (VBUS), J23.B4 (VBUS), J23.B9 (VBUS), R8.1
unnamed: Module1.21 (PI_nLED_Activity), R1.2
unnamed: P1.A6 (D+), U4#2.4 (D2+), U4#2.7
unnamed: P1.A7 (D-), U4#2.5 (D2-), U4#2.6
unnamed: P1.A4 (VBUS), P1.A9 (VBUS), P1.B4 (VBUS), P1.B9 (VBUS)
unnamed: Q1#2.1 (B), R41.1
unnamed: C36.1, J19#2.1, Q1.5 (D)
unnamed: Q1#2.2 (E), R40.1, U15.12 (DTR)
unnamed: Q2.1 (B), R40.2
unnamed: Q2.2 (E), R41.2, U15.13 (RTS)
unnamed: R10.2, U5.4
unnamed: R2.1, U3.16 (LEDG_K)
unnamed: R3.1, U3.18 (LEDY_K)
unnamed: U4.4 (D2+), U4.7
unnamed: U4.5 (D2-), U4.6
unnamed: R16.1, U6.25 (HS_IND/CFG_SEL1)
unnamed: R15.2, U6.35 (RBIAS)
unnamed: R12.1, U6.24 (SCL/SMBCLK/CFG_SEL0)
unnamed: R13.1, U6.22 (SDA/SMBDATA/NON_REM1)
unnamed: R14.1, U6.28 (SUSP_IND/LOCAL_PWR/NON_REM0)
unnamed: C8.1, U6.33 (XTALIN/CLKIN), Y1.1
unnamed: C9.1, U6.32 (XTALOUT), Y1.2
unnamed: R36.1, U7.5 (ILIM)
unnamed: R43.2, U8.8 (IO15)
unnamed: C22.2, C31.2, U10.1 (BST), U10#2.1 (BST)
unnamed: C25#2.1, C33#2.1, R23.1, R23#2.1, U10.6 (COMP), U10#2.6 (COMP)
unnamed: C27.2, C44.2, R24.2, R24#2.2, R30.1, R30#2.1, U10.5 (FB), U10#2.5 (FB)
unnamed: C24.1, C32.1, U10.4 (SS), U10#2.4 (SS)
unnamed: L1.1, L1#2.1, R22.1, R22#2.1, U10.8 (SW), U10#2.8 (SW)
unnamed: C14.2, U14.1 (BST)
unnamed: C17.1, R25.1, U14.6 (COMP)
unnamed: C19.2, R27#2.2, R28.1, U14.5 (FB)
unnamed: C15.1, U14.4 (SS)
unnamed: L2.1, R9#2.1, U14.8 (SW)
unnamed: C3.1, U15.6 (V3)
unnamed: C30.2, C57.2, U16.1 (BST), U16#2.1 (BST)
unnamed: C32#2.1, C59.1, R25#2.1, R39.1, U16.6 (COMP), U16#2.6 (COMP)
unnamed: C34.2, C61.2, R27.2, R28#2.1, R45.2, R46.1, U16.5 (FB), U16#2.5 (FB)
unnamed: C31#2.1, C58.1, U16.4 (SS), U16#2.4 (SS)
unnamed: L3.1, L5.1, R9.1, R35.1, U16.8 (SW), U16#2.8 (SW)
unnamed: U35.3 (GND), U35.8 (GND)
unnamed: J19.A7 (D-), J19.B7 (D-), U38.8 (HSD1_M), U39.5 (D2-), U39.6
unnamed: J19.A6 (D+), J19.B6 (D+), U38.9 (HSD1_P), U39.4 (D2+), U39.7
unnamed: R62.1, R63.2, U38.2 (SEL)
unnamed: J20.A6 (D+), J20.B6 (D+), U39.1 (D1+), U39.10, U40.9 (HSD1_P)
unnamed: J20.A7 (D-), J20.B7 (D-), U39.2 (D1-), U39.9, U40.8 (HSD1_M)
unnamed: U39.3 (GND), U39.8 (GND)
unnamed: R66.1, R67.2, U40.2 (SEL)
unnamed: U42.1 (GND), U42.7 (GND)
unnamed: U49.1 (GND), U49.7 (GND)
unnamed: U50.1 (GND), U50.7 (GND)
unnamed: U51.1 (GND), U51.7 (GND)

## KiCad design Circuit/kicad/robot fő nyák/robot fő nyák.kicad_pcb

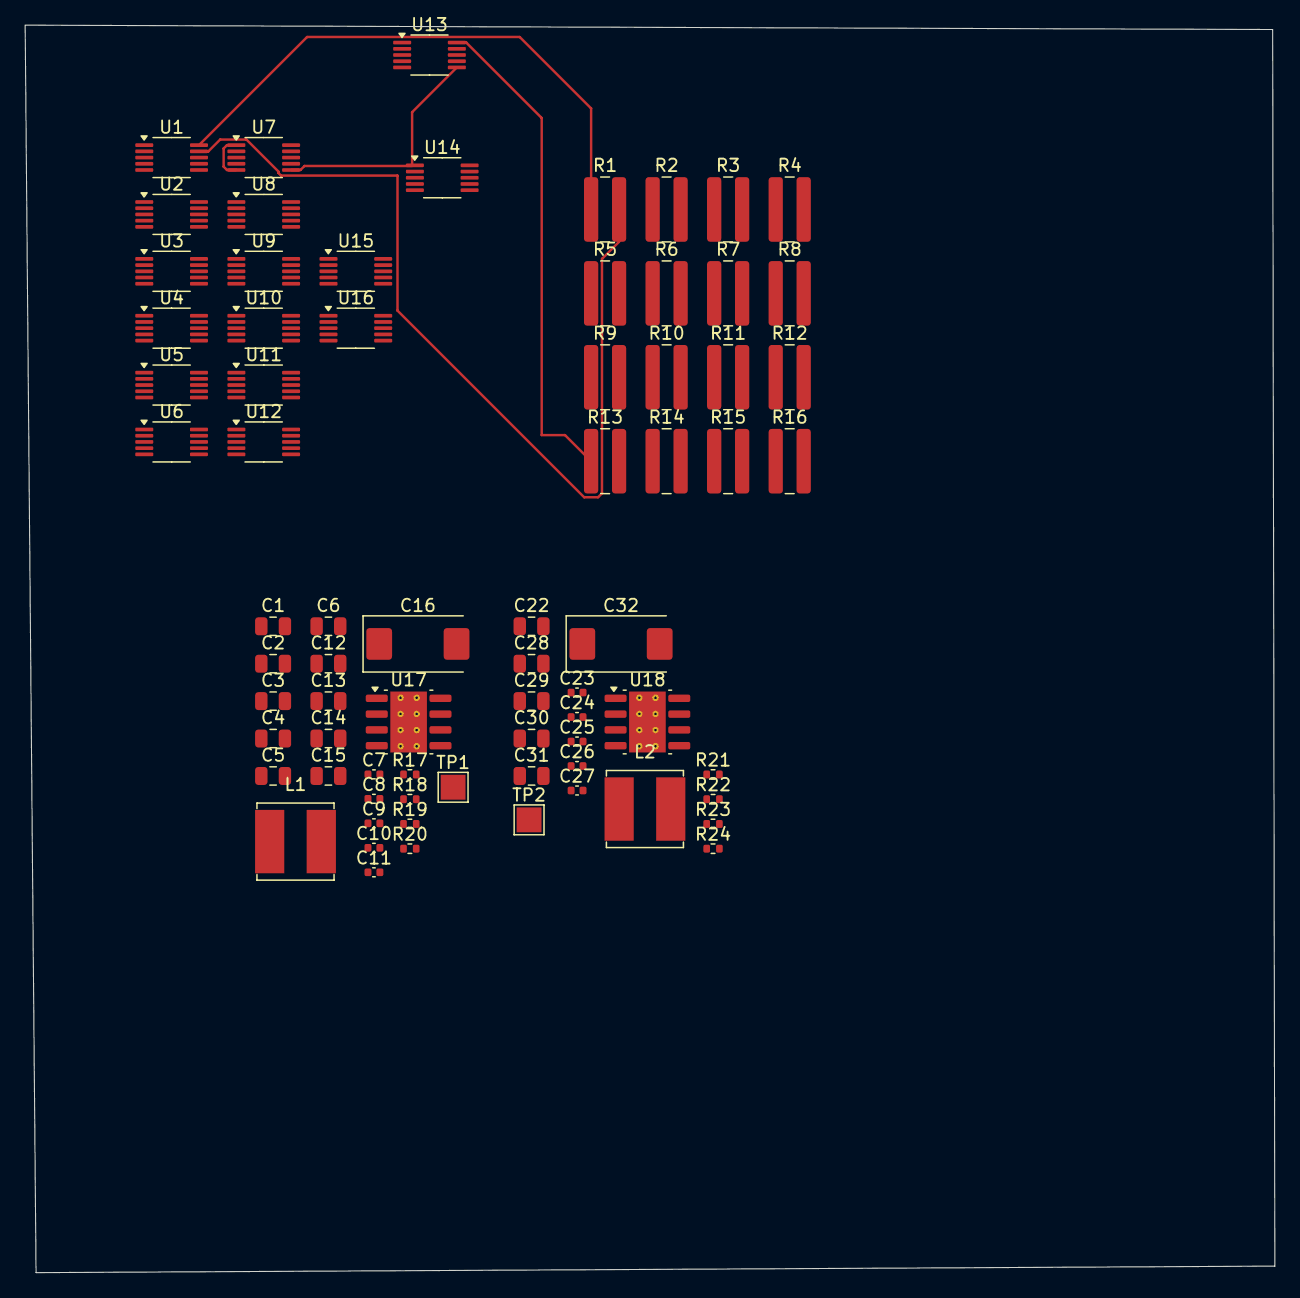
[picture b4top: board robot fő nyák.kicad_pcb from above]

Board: 2 copper layers, 100.5 x 100.4 mm, 73 parts (0 on the bottom side), 47 nets.

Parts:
C1, C2, C3, C4, C5, C6: 10u 35v; C_0805_2012Metric
C7, C8, C23, C24: 100n; C_0402_1005Metric
C9, C11, C25, C27: nf; C_0402_1005Metric
C10, C26: 1.2nF; C_0402_1005Metric
C12, C13, C14, C15, C28, C29, C30, C31: 10u; C_0805_2012Metric
C16, C32: 100uF; CP_EIA-7343-31_Kemet-D
C22: 100uF 16V; C_0805_2012Metric
L1, L2: SRN6045TA-3R3Y; L_Bourns_SRN6045TA
R1, R2, R3, R4, R5, R6, R7, R8, R9, R10, R11, R12, R13, R14, R15, R16: 0.025Ω; R_1020_2550Metric
R17, R21: 10R; R_0402_1005Metric
R18, R22: 20K 1%; R_0402_1005Metric
R19: 12K 1%; R_0402_1005Metric
R20: 2.2K 1%; R_0402_1005Metric
R23: 10K 1%; R_0402_1005Metric
R24: 3K 1%; R_0402_1005Metric
TP1, TP2: TestPoint; TestPoint_Pad_2.0x2.0mm
U1, U2, U3, U4, U5, U6, U7, U8, U9, U10, U11, U12, U13, U14, U15, U16: INA226; VSSOP-10_3x3mm_P0.5mm
U17, U18: AP64501SP-13; SOIC-8-1EP_3.9x4.9mm_P1.27mm_EP2.95x4.9mm_Mask2.71x3.4mm_Th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

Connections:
5V1: U1.6 (VS), U2.1 (A1), U2.6 (VS), U3.6 (VS), U4.6 (VS), U5.2 (A0), U5.6 (VS), U6.1 (A1), U6.2 (A0), U6.6 (VS), U7.2 (A0), U7.6 (VS), U8.2 (A0), U8.6 (VS), U9.6 (VS), U10.1 (A1), U10.6 (VS), U11.6 (VS), U12.6 (VS), U13.6 (VS), U14.1 (A1), U14.6 (VS), U15.6 (VS), U16.6 (VS)
/3v3_psu/3V3_psu: C27.1, C28.1, C29.1, C30.1, C31.1, C32.1, L2.2, R7.2, R23.1, TP2.1, U7.9 (Vin-)
/3v3_psu/bat in +: C1.1, C2.1, C3.1, C4.1, C5.1, C6.1, C22.1, R9.1, U9.8 (Vbus), U9.10 (Vin+), U17.2 (VIN), U17.3 (EN), U18.2 (VIN), U18.3 (EN)
/4pcs TMC2240/M2+: R5.1, U5.8 (Vbus), U5.10 (Vin+)
/4pcs TMC2240/M3+: R3.1, U3.8 (Vbus), U3.10 (Vin+)
/4pcs TMC2240/M4+: R4.1, U4.8 (Vbus), U4.10 (Vin+)
/5V_psu/5V_psu +: C11.1, C12.1, C13.1, C14.1, C15.1, C16.1, L1.2, R14.2, R19.1, TP1.1, U14.9 (Vin-)
/INA226/+1000000: R1.1, U1.8 (Vbus), U1.10 (Vin+)
/INA226/+1000011: R13.1, U13.8 (Vbus), U13.10 (Vin+)
/INA226/+1000100: R2.1, U2.8 (Vbus), U2.10 (Vin+)
/INA226/+1000101: R6.1, U6.8 (Vbus), U6.10 (Vin+)
/INA226/+1000110: R10.1, U10.8 (Vbus), U10.10 (Vin+)
/INA226/+1000111: R14.1, U14.8 (Vbus), U14.10 (Vin+)
/INA226/+1001001: R7.1, U7.8 (Vbus), U7.10 (Vin+)
/INA226/+1001010: R11.1, U11.8 (Vbus), U11.10 (Vin+)
/INA226/+1001011: R15.1, U15.8 (Vbus), U15.10 (Vin+)
/INA226/+1001101: R8.1, U8.8 (Vbus), U8.10 (Vin+)
/INA226/+1001110: R12.1, U12.8 (Vbus), U12.10 (Vin+)
/INA226/+1001111: R16.1, U16.8 (Vbus), U16.10 (Vin+)
/INA226/-1000000: R1.2, R3.2, R4.2, R5.2, R9.2, U1.9 (Vin-), U3.9 (Vin-), U4.9 (Vin-), U5.9 (Vin-), U9.9 (Vin-)
/INA226/-1000011: R13.2, U13.9 (Vin-)
/INA226/-1000100: R2.2, U2.9 (Vin-)
/INA226/-1000101: R6.2, U6.9 (Vin-)
/INA226/-1000110: R10.2, U10.9 (Vin-)
/INA226/-1001010: R11.2, U11.9 (Vin-)
/INA226/-1001011: R15.2, U15.9 (Vin-)
/INA226/-1001101: R8.2, U8.9 (Vin-)
/INA226/-1001110: R12.2, U12.9 (Vin-)
/INA226/-1001111: R16.2, U16.9 (Vin-)
/INA226/alert out: U1.3 (~Alert), U2.3 (~Alert), U3.3 (~Alert), U4.3 (~Alert), U5.3 (~Alert), U6.3 (~Alert), U7.3 (~Alert), U8.3 (~Alert), U9.3 (~Alert), U10.3 (~Alert), U11.3 (~Alert), U12.3 (~Alert), U13.3 (~Alert), U14.3 (~Alert), U15.3 (~Alert), U16.3 (~Alert)
GND: C1.2, C2.2, C3.2, C4.2, C5.2, C6.2, C8.2, C9.2, C10.2, C12.2, C13.2, C14.2, C15.2, C16.2, C22.2, C24.2, C25.2, C26.2, C28.2, C29.2, C30.2, C31.2, C32.2, R20.2, R24.2, U1.1 (A1), U1.2 (A0), U1.7 (GND), U2.2 (A0), U2.7 (GND), U3.2 (A0), U3.7 (GND), U4.2 (A0), U4.7 (GND), U5.1 (A1), U5.7 (GND), U6.7 (GND), U7.7 (GND), U8.7 (GND), U9.1 (A1), U9.7 (GND), U10.7 (GND), U11.7 (GND), U12.7 (GND), U13.1 (A1), U13.7 (GND), U14.7 (GND), U15.7 (GND), U16.7 (GND), U17.7 (GND), U17.9 (EP), U18.7 (GND), U18.9 (EP)
INA226_SCL: U1.4 (SDA), U2.4 (SDA), U3.4 (SDA), U4.1 (A1), U4.4 (SDA), U5.4 (SDA), U6.4 (SDA), U7.4 (SDA), U8.1 (A1), U8.4 (SDA), U9.4 (SDA), U10.4 (SDA), U11.4 (SDA), U12.1 (A1), U12.4 (SDA), U13.2 (A0), U13.4 (SDA), U14.2 (A0), U14.4 (SDA), U15.2 (A0), U15.4 (SDA), U16.1 (A1), U16.2 (A0), U16.4 (SDA)
INA226_SDA: U1.5 (SCL), U2.5 (SCL), U3.1 (A1), U3.5 (SCL), U4.5 (SCL), U5.5 (SCL), U6.5 (SCL), U7.1 (A1), U7.5 (SCL), U8.5 (SCL), U9.2 (A0), U9.5 (SCL), U10.2 (A0), U10.5 (SCL), U11.1 (A1), U11.2 (A0), U11.5 (SCL), U12.2 (A0), U12.5 (SCL), U13.5 (SCL), U14.5 (SCL), U15.1 (A1), U15.5 (SCL), U16.5 (SCL)
unnamed: C7.1, R17.2
unnamed: C10.1, R18.2
unnamed: C23.1, R21.2
unnamed: C26.1, R22.2
unnamed: C7.2, U17.1 (BST)
unnamed: C9.1, R18.1, U17.6 (COMP)
unnamed: C11.2, R19.2, R20.1, U17.5 (FB)
unnamed: C8.1, U17.4 (SS)
unnamed: L1.1, R17.1, U17.8 (SW)
unnamed: C23.2, U18.1 (BST)
unnamed: C25.1, R22.1, U18.6 (COMP)
unnamed: C27.2, R23.2, R24.1, U18.5 (FB)
unnamed: C24.1, U18.4 (SS)
unnamed: L2.1, R21.1, U18.8 (SW)
